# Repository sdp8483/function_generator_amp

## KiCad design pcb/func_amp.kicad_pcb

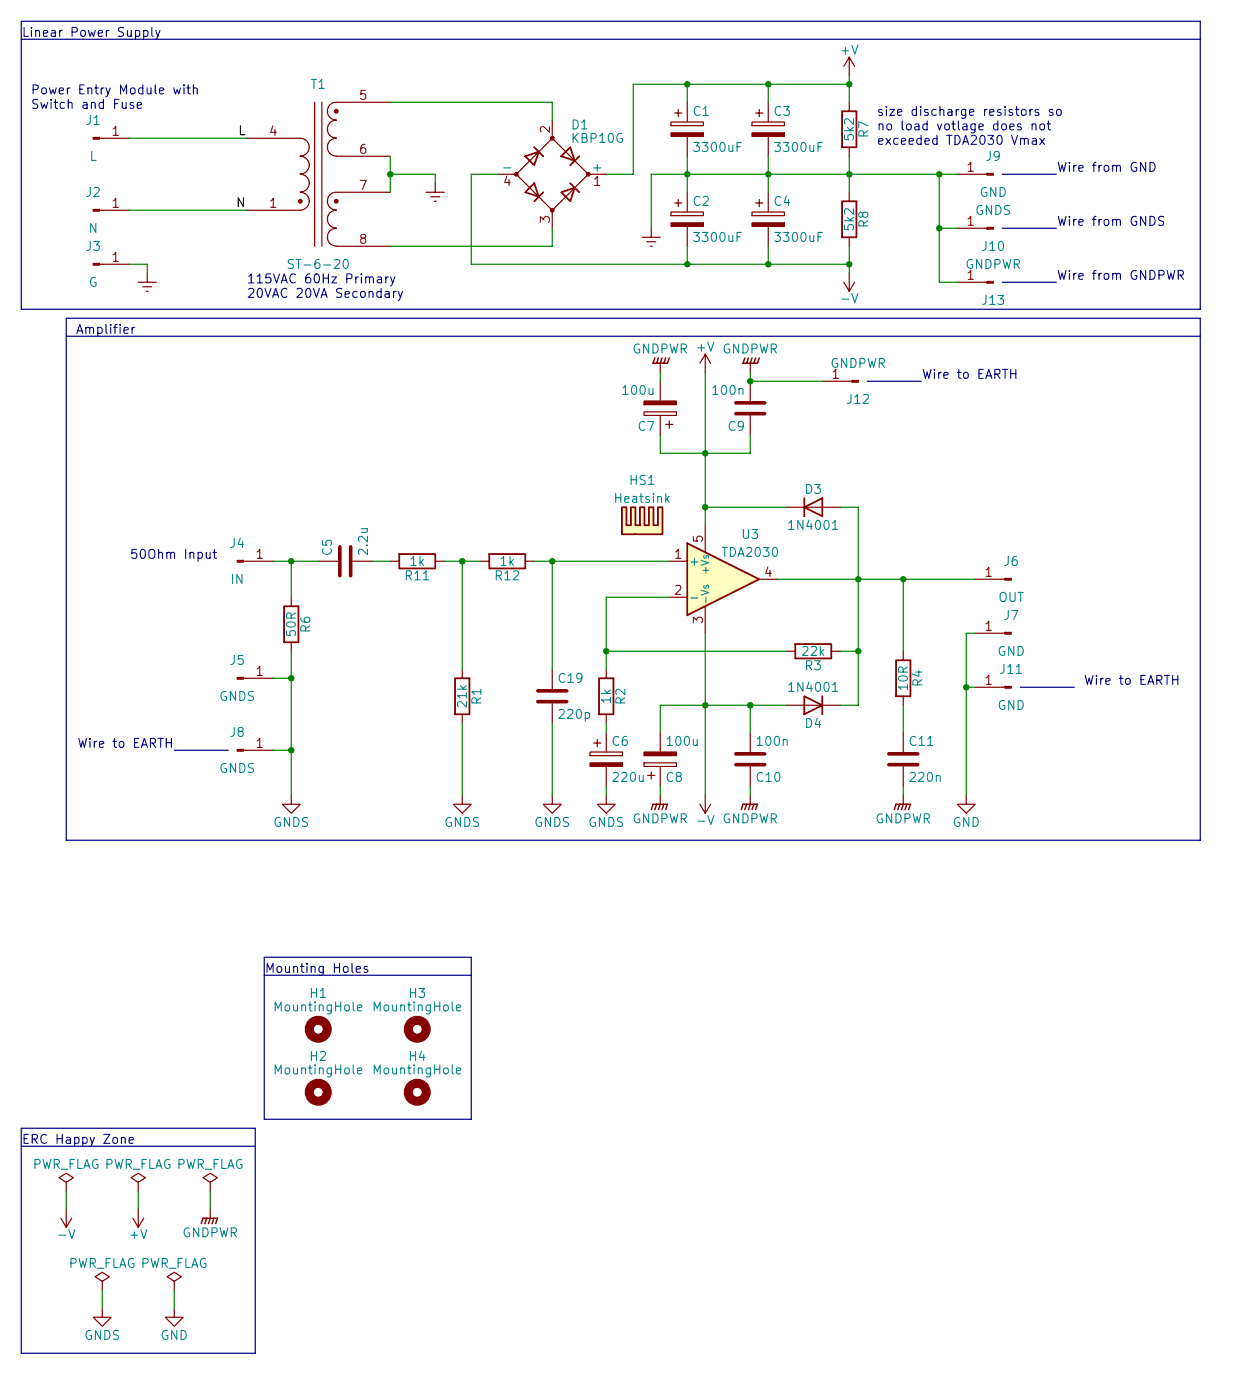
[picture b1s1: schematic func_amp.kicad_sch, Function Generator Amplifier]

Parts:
C1, C2, C3, C4: 3300uF; CP_Radial_D18.0mm_P7.50mm
C5: 2.2u; C_Rect_L31.5mm_W11.0mm_P27.50mm_MKS4
C6: 220u; CP_Radial_D8.0mm_P3.80mm
C7, C8: 100u; CP_Radial_D8.0mm_P3.80mm
C9, C10: 100n; C_Rect_L13.0mm_W4.0mm_P10.00mm_FKS3_FKP3_MKS4
C11: 220n; C_Rect_L13.0mm_W8.0mm_P10.00mm_FKS3_FKP3_MKS4
C19: 220p; C_Rect_L7.2mm_W4.5mm_P5.00mm_FKS2_FKP2_MKS2_MKP2
D1: KBP10G; Diode_Bridge_Vishay_KBPM
D3, D4: 1N4001; D_DO-41_SOD81_P10.16mm_Horizontal
H1, H2, H3, H4: MountingHole; MountingHole_3.2mm_M3
HS1: Heatsink; random_psu_heatsink
J1: L; TE_0.25in_spade_63824-1
J2: N; TE_0.25in_spade_63824-1
J3: G; TE_0.25in_spade_63824-1
J4: IN; TE_0.25in_spade_63824-1
J5, J8, J10: GNDS; TE_0.25in_spade_63824-1
J6: OUT; TE_0.25in_spade_63824-1
J7, J9, J11: GND; TE_0.25in_spade_63824-1
J12, J13: GNDPWR; TE_0.25in_spade_63824-1
R1: 21k; R_Axial_DIN0207_L6.3mm_D2.5mm_P10.16mm_Horizontal
R2, R11, R12: 1k; R_Axial_DIN0207_L6.3mm_D2.5mm_P10.16mm_Horizontal
R3: 22k; R_Axial_DIN0207_L6.3mm_D2.5mm_P10.16mm_Horizontal
R4: 10R; R_Axial_DIN0411_L9.9mm_D3.6mm_P15.24mm_Horizontal
R6: 50R; R_Axial_DIN0207_L6.3mm_D2.5mm_P10.16mm_Horizontal
R7, R8: 5k2; R_Axial_DIN0207_L6.3mm_D2.5mm_P10.16mm_Horizontal
T1: ST-6-20
U3: TDA2030; TO-220-5_P3.4x3.7mm_StaggerOdd_Lead3.8mm_Vertical

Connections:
+V: C1.1, C3.1, C7.1, C9.1, D1.1 (+), D3.1 (K), R7.1, U3.5 (+Vs)
-V: C2.2, C4.2, C8.2, C10.2, D1.4 (-), D4.2 (A), R8.2, U3.3 (-Vs)
/L: J1.1, T1.4 (AB)
/N: J2.1, T1.1 (AA)
Earth: C1.2, C2.1, C3.2, C4.1, J3.1, J9.1, J10.1, J13.1, R7.2, R8.1, T1.6 (SB), T1.7 (SC)
GND: J7.1, J11.1
GNDPWR: C7.2, C8.1, C9.2, C10.1, C11.2, J12.1
GNDS: C6.2, C19.2, J5.1, J8.1, R1.2, R6.2
unnamed: C5.1, J4.1, R6.1
unnamed: C5.2, R11.2
unnamed: C6.1, R2.2
unnamed: C11.1, R4.2
unnamed: C19.1, R12.1, U3.1 (+)
unnamed: D1.2, T1.5 (SA)
unnamed: D1.3, T1.8 (SD)
unnamed: D3.2 (A), D4.1 (K), J6.1, R3.1, R4.1, U3.4
unnamed: R1.1, R11.1, R12.2
unnamed: R2.1, R3.2, U3.2 (-)

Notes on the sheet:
Linear Power Supply
size discharge resistors so no load votlage does not exceeded TDA2030 Vmax
Amplifier
Wire to EARTH
Mounting Holes
Wire from GNDPWR
ERC Happy Zone
115VAC 60Hz Primary 20VAC 20VA Secondary
Power Entry Module with Switch and Fuse
50Ohm Input
Wire from GND
Wire from GNDS

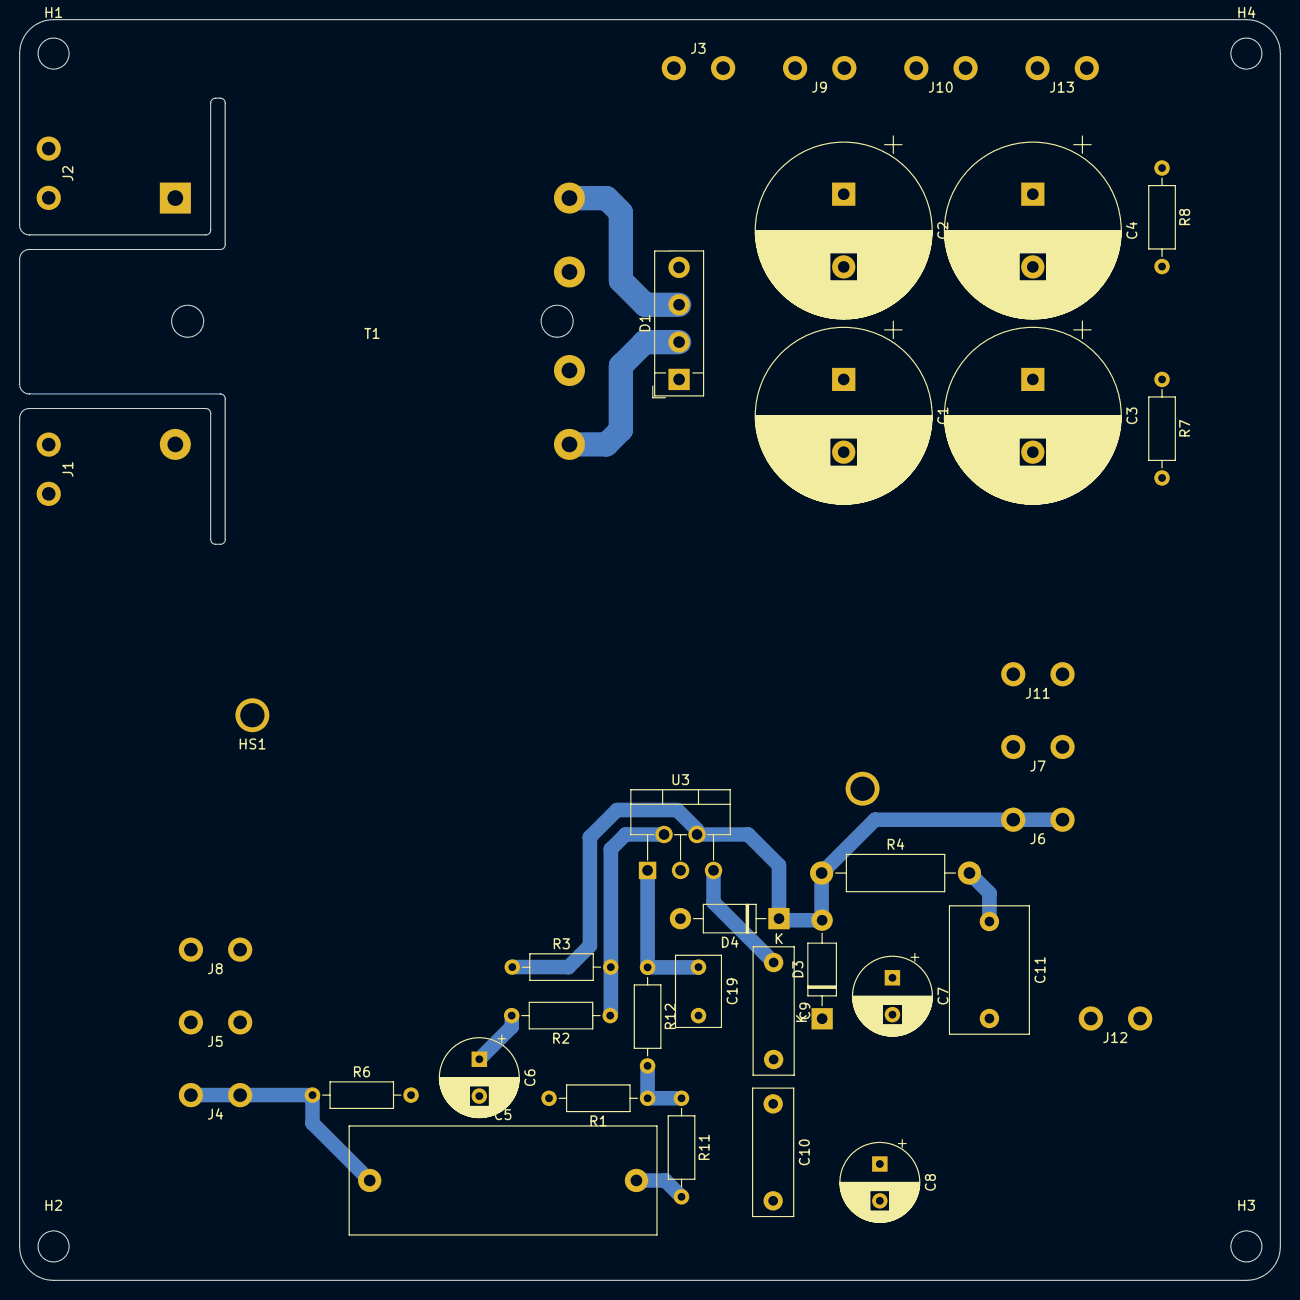
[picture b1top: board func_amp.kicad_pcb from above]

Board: 2 copper layers, 130.0 x 130.0 mm, 44 parts (0 on the bottom side), 18 nets.

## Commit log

2021-11-16 init commit
2021-11-16 schematic
2021-11-21 init pcb layout and gerber
2021-11-21 generate gcode for 3018
2021-11-21 create ibom
2021-11-24 update with available component value
2021-12-06 xformer 3d shape
2021-12-06 +-V symbols
2021-12-06 xformer symbol
2021-12-06 update schema
2021-12-08 update footprints
2021-12-12 create heatsink model
2021-12-12 add heatsink
2021-12-12 add spade terminal 3d model
2021-12-12 spade grounds for star ground
2021-12-13 create 3d model
2021-12-13 spade star grounds
2021-12-13 pcb layout
2021-12-19 new gerbers
2022-01-30 ignore backups
2022-01-30 update to KiCAD V6
2022-02-09 fix shroud
2022-02-19 performance testing
2023-10-20 ignore all .lck
2023-10-20 cleanup schematic
2023-10-20 export to PDF
2023-10-20 update gerbers
2023-10-20 generate gcode
2023-11-18 printed parts dim changes
